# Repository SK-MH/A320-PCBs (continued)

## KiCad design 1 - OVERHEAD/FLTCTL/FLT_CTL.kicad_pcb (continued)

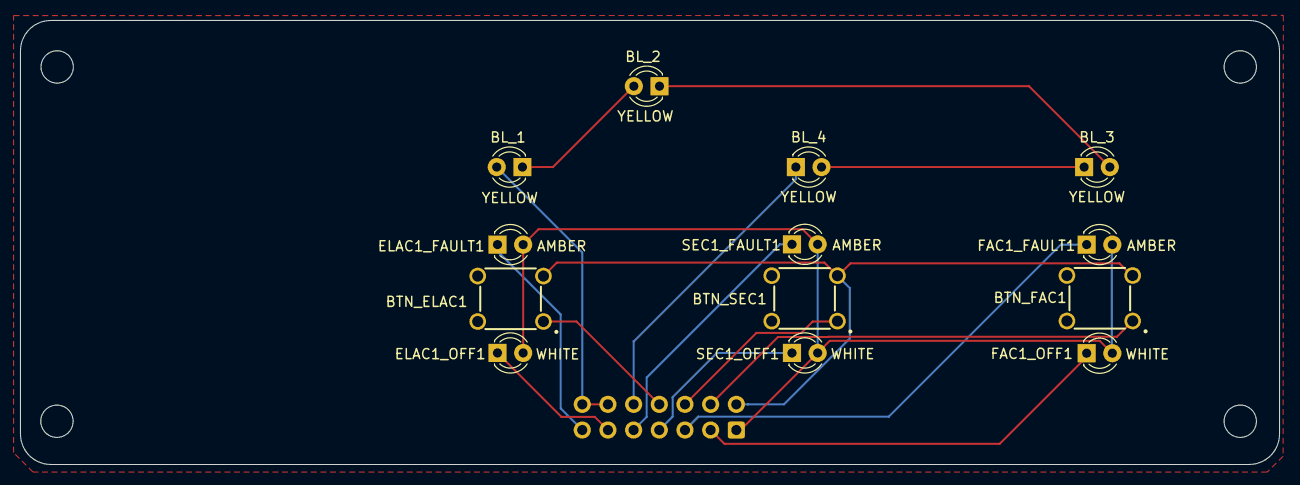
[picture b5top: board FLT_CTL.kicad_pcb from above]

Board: 2 copper layers, 124.6 x 43.9 mm, 14 parts (1 on the bottom side), 16 nets.

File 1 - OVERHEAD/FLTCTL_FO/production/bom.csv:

Designator,Footprint,Quantity,Value,LCSC Part #
"BL_1, BL_2, BL_3, BL_4",LED_D3.0mm,4,YELLOW,
"BTN_ELAC2, BTN_FAC2, BTN_SEC2, BTN_SEC3",B3F1000,4,B3F-1055,
"ELAC2_FAULT1, FAC2_FAULT1, SEC2_FAULT1, SEC3_FAULT1",LED_D3.0mm,4,AMBER,
"ELAC2_OFF1, FAC2_OFF1, SEC2_OFF1, SEC3_OFF1",LED_D3.0mm,4,WHITE,
FLT_CTL_FO1,IDC-Header_2x08_P2.54mm_Vertical,1,Pin Header,

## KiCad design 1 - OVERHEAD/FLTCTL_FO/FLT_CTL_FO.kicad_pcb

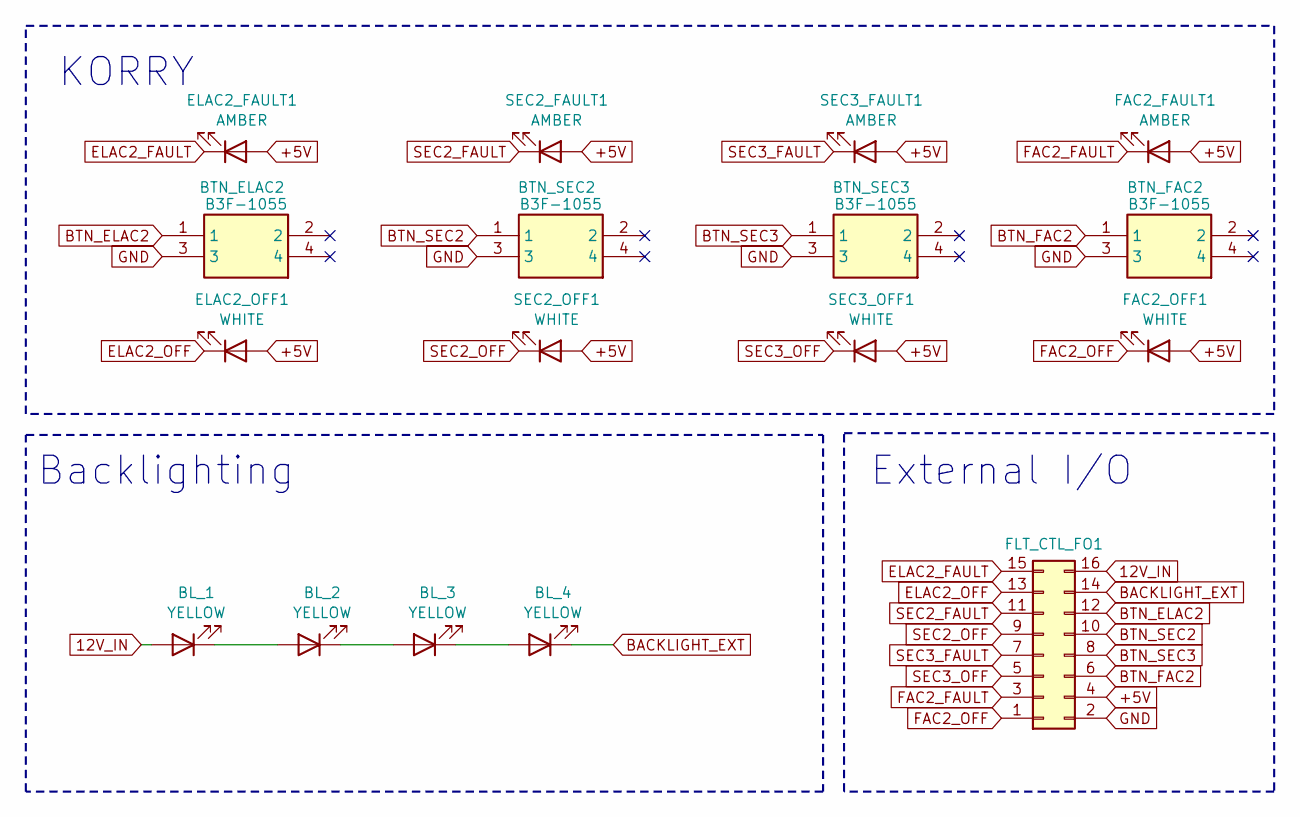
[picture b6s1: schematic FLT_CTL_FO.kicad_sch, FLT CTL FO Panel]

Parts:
BL_1, BL_2, BL_3, BL_4: YELLOW; LED_D3.0mm
BTN_ELAC2: B3F-1055; B3F1000; Mouser Part Number 653-B3F-1055
BTN_FAC2: B3F-1055; B3F1000; Mouser Part Number 653-B3F-1055
BTN_SEC2, BTN_SEC3: B3F-1055; B3F1000; Mouser Part Number 653-B3F-1055
ELAC2_FAULT1: AMBER; LED_D3.0mm
ELAC2_OFF1: WHITE; LED_D3.0mm
FAC2_FAULT1: AMBER; LED_D3.0mm
FAC2_OFF1: WHITE; LED_D3.0mm
FLT_CTL_FO1: Pin Header; IDC-Header_2x08_P2.54mm_Vertical
SEC2_FAULT1, SEC3_FAULT1: AMBER; LED_D3.0mm
SEC2_OFF1, SEC3_OFF1: WHITE; LED_D3.0mm

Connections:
12V_IN: BL_1.2 (A), FLT_CTL_FO1.16
+5V: ELAC2_FAULT1.2 (A), ELAC2_OFF1.2 (A), FAC2_FAULT1.2 (A), FAC2_OFF1.2 (A), FLT_CTL_FO1.4, SEC2_FAULT1.2 (A), SEC2_OFF1.2 (A), SEC3_FAULT1.2 (A), SEC3_OFF1.2 (A)
BACKLIGHT_EXT: BL_4.1 (K), FLT_CTL_FO1.14
BTN_ELAC2: BTN_ELAC2.1, FLT_CTL_FO1.12
BTN_FAC2: BTN_FAC2.1, FLT_CTL_FO1.6
BTN_SEC2: BTN_SEC2.1, FLT_CTL_FO1.10
BTN_SEC3: BTN_SEC3.1, FLT_CTL_FO1.8
ELAC2_FAULT: ELAC2_FAULT1.1 (K), FLT_CTL_FO1.15
ELAC2_OFF: ELAC2_OFF1.1 (K), FLT_CTL_FO1.13
FAC2_FAULT: FAC2_FAULT1.1 (K), FLT_CTL_FO1.3
FAC2_OFF: FAC2_OFF1.1 (K), FLT_CTL_FO1.1
GND: BTN_ELAC2.3, BTN_FAC2.3, BTN_SEC2.3, BTN_SEC3.3, FLT_CTL_FO1.2
unnamed: BL_1.1 (K), BL_2.2 (A)
unnamed: BL_2.1 (K), BL_3.2 (A)
unnamed: BL_3.1 (K), BL_4.2 (A)
SEC2_FAULT: FLT_CTL_FO1.11, SEC2_FAULT1.1 (K)
SEC2_OFF: FLT_CTL_FO1.9, SEC2_OFF1.1 (K)
SEC3_FAULT: FLT_CTL_FO1.7, SEC3_FAULT1.1 (K)
SEC3_OFF: FLT_CTL_FO1.5, SEC3_OFF1.1 (K)

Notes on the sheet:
Backlighting
External I/O
KORRY

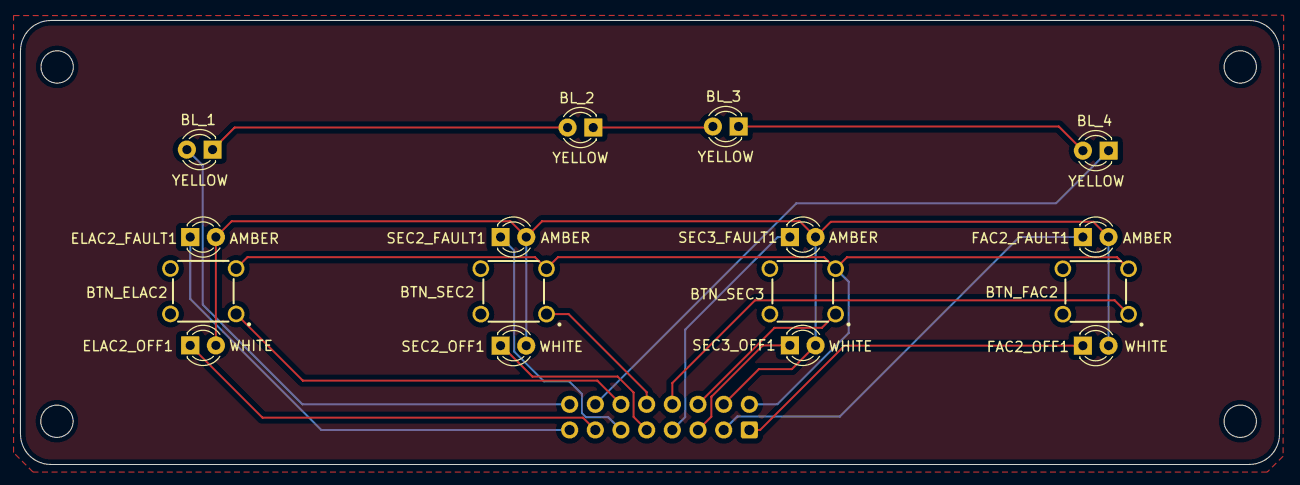
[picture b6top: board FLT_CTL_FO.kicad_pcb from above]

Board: 2 copper layers, 124.6 x 43.9 mm, 17 parts (1 on the bottom side), 19 nets.

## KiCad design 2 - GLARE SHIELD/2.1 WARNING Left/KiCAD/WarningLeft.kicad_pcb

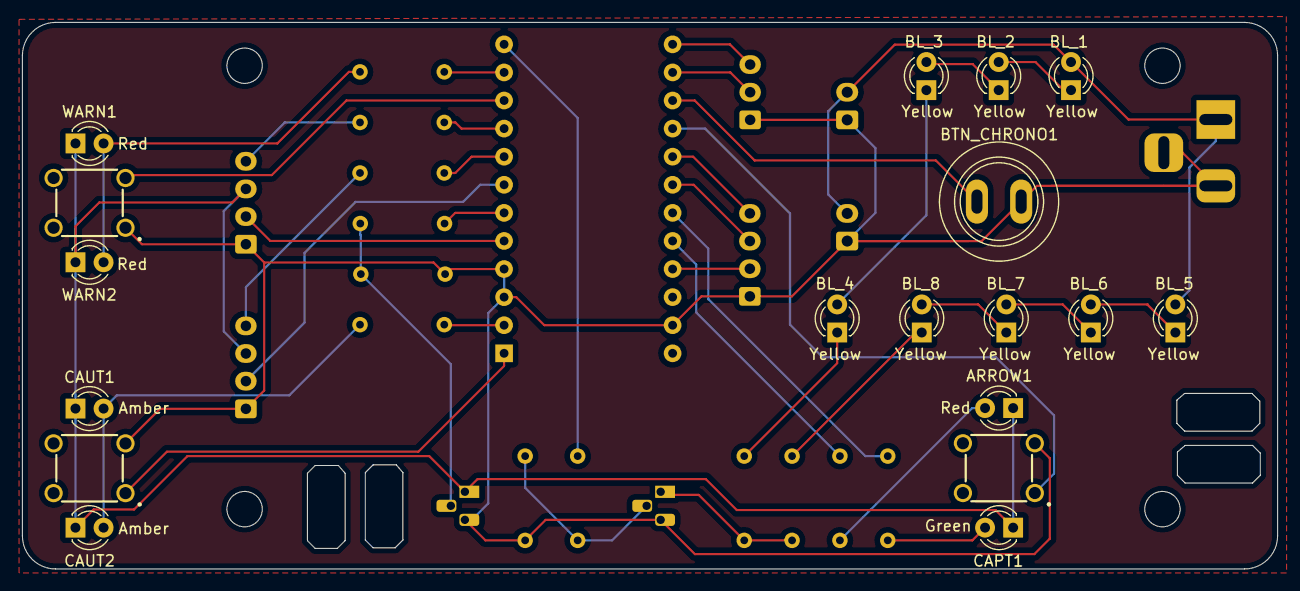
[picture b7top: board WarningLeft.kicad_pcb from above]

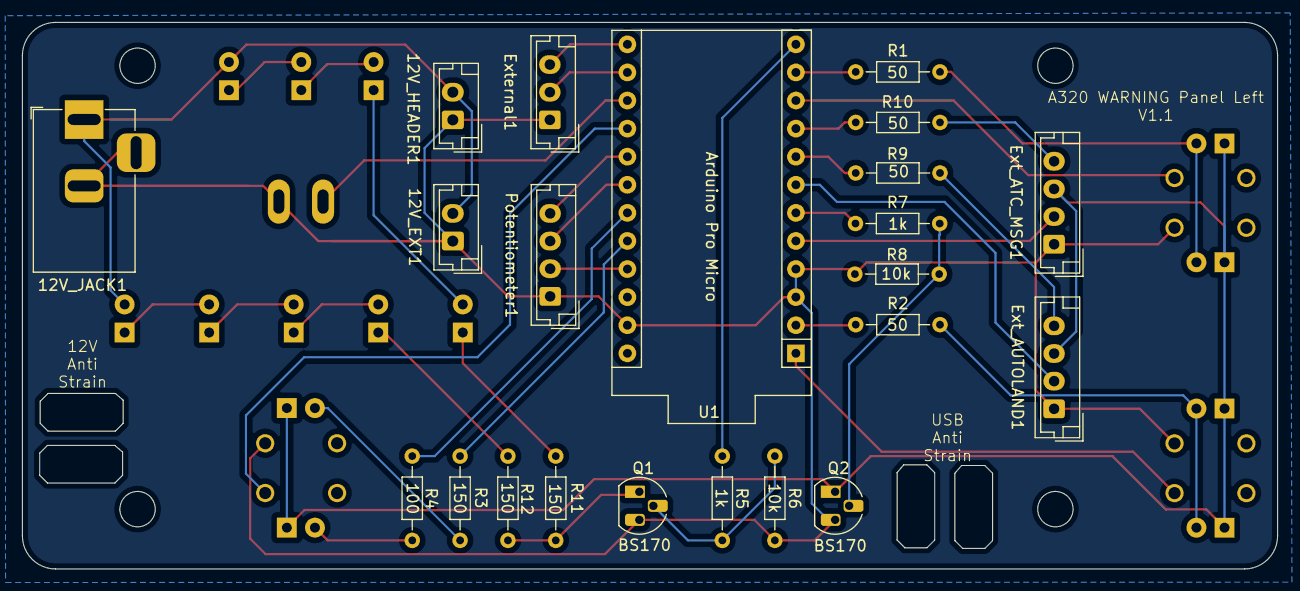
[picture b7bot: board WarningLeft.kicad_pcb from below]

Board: 2 copper layers, 113.5 x 49.4 mm, 40 parts (22 on the bottom side), 39 nets.

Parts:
12V_EXT1, 12V_HEADER1: Pin Header 1x02; JST_EH_B2B-EH-A_1x02_P2.50mm_Vertical
12V_JACK1: Power Jack; BarrelJack_Horizontal
ARROW1: Red; LED_D3.0mm
BL_1, BL_2, BL_3, BL_4, BL_5, BL_6, BL_7, BL_8: Yellow; LED_D3.0mm
BTN_CAUT1: B3F-1055; B3F1000
BTN_CHRONO1: Push Button; SW-Push
BTN_SIDESTICK1: B3F-1055; B3F1000
BTN_WARN1: B3F-1055; B3F1000
CAPT1: Green; LED_D3.0mm
CAUT1, CAUT2: Amber; LED_D3.0mm
Ext_ATC_MSG1: Pin Header 1x04; JST_EH_B4B-EH-A_1x04_P2.50mm_Vertical
Ext_AUTOLAND1: Pin Header 1x04; JST_EH_B4B-EH-A_1x04_P2.50mm_Vertical
External1: Pin Header 1x03; JST_EH_B3B-EH-A_1x03_P2.50mm_Vertical
Potentiometer1: Pin Header 1x04; JST_EH_B4B-EH-A_1x04_P2.50mm_Vertical
Q1, Q2: BS170; TO-92_HandSolder
R1, R2, R9, R10: 50; R_Axial_DIN0204_L3.6mm_D1.6mm_P7.62mm_Horizontal
R3, R11, R12: 150; R_Axial_DIN0204_L3.6mm_D1.6mm_P7.62mm_Horizontal
R4: 100; R_Axial_DIN0204_L3.6mm_D1.6mm_P7.62mm_Horizontal
R5, R7: 1k; R_Axial_DIN0204_L3.6mm_D1.6mm_P7.62mm_Horizontal
R6, R8: 10k; R_Axial_DIN0204_L3.6mm_D1.6mm_P7.62mm_Horizontal
U1: Arduino Pro Micro; Sparkfun_Pro_Micro
WARN1, WARN2: Red; LED_D3.0mm

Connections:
12V_IN: 12V_EXT1.2, 12V_HEADER1.2, 12V_JACK1.1, BL_1.2 (A), BL_5.2 (A)
+5V: Potentiometer1.2, U1.21 (VCC)
ARROW: R3.1, U1.20 (D21/A3)
ATC_MSG: R10.2, U1.9 (~D6/A7)
AUTOLAND: R9.2, U1.8 (~D5)
BACKLIGHT_GND: Q1.1 (D), R11.2, R12.2
BTN_ATC_MSG: Ext_ATC_MSG1.2, U1.5 (D2)
BTN_AUTOLAND: Ext_AUTOLAND1.2, U1.7 (D4/A6)
BTN_CAUT: BTN_CAUT1.1, U1.1 (D1/TX)
BTN_CHRONO: BTN_CHRONO1.1, U1.15 (D14)
BTN_SIDESTICK: BTN_SIDESTICK1.1, U1.16 (D15)
BTN_WARN: BTN_WARN1.3, U1.10 (D7)
CAUT: R2.1, U1.2 (D0/RX)
EXT1: External1.2, U1.14 (D16)
EXT2: External1.3, U1.13 (~D10/A10)
GND: 12V_EXT1.1, 12V_HEADER1.1, 12V_JACK1.2, 12V_JACK1.3, BTN_CAUT1.3, BTN_CHRONO1.2, BTN_SIDESTICK1.3, BTN_WARN1.1, Ext_ATC_MSG1.1, Ext_AUTOLAND1.1, External1.1, Potentiometer1.1, Q1.3 (S), Q2.3 (S), R6.1, R8.1, U1.3 (GND), U1.4 (GND), U1.23 (GND)
LED_GND: ARROW1.1 (K), CAPT1.1 (K), CAUT1.1 (K), CAUT2.1 (K), Ext_ATC_MSG1.3, Ext_AUTOLAND1.3, Q2.1 (D), WARN1.1 (K), WARN2.1 (K)
unnamed: ARROW1.2 (A), R3.2
unnamed: BL_1.1 (K), BL_2.2 (A)
unnamed: BL_2.1 (K), BL_3.2 (A)
unnamed: BL_3.1 (K), BL_4.2 (A)
unnamed: BL_4.1 (K), R11.1
unnamed: BL_5.1 (K), BL_6.2 (A)
unnamed: BL_6.1 (K), BL_7.2 (A)
unnamed: BL_7.1 (K), BL_8.2 (A)
unnamed: BL_8.1 (K), R12.1
unnamed: CAPT1.2 (A), R4.2
unnamed: CAUT1.2 (A), CAUT2.2 (A), R2.2
unnamed: Ext_ATC_MSG1.4, R10.1
unnamed: Ext_AUTOLAND1.4, R9.1
unnamed: Q1.2 (G), R5.2, R6.2
unnamed: Q2.2 (G), R7.2, R8.2
unnamed: R1.2, WARN1.2 (A), WARN2.2 (A)
OUT_BRT_BACK: R5.1, U1.12 (~D9/A9)
OUT_BRT_LED: R7.1, U1.6 (~D3)
POT1: Potentiometer1.3, U1.18 (D19/A1)
POT2: Potentiometer1.4, U1.17 (D18/A0)
PRIO: R4.1, U1.19 (D20/A2)
WARN: R1.1, U1.11 (D8/A8)

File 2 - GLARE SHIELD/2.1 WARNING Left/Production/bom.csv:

Designator,Footprint,Quantity,Value,LCSC Part #
"12V_EXT1, 12V_HEADER1",JST_EH_B2B-EH-A_1x02_P2.50mm_Vertical,2,Pin Header 1x02,
12V_JACK1,BarrelJack_Horizontal,1,Power Jack,
"ARROW1, WARN1, WARN2",LED_D3.0mm,3,Red,
"BL_1, BL_2, BL_3, BL_4, BL_5, BL_6, BL_7, BL_8",LED_D3.0mm,8,Yellow,
"BTN_CAUT1, BTN_SIDESTICK1, BTN_WARN1",B3F1000,3,B3F-1055,
BTN_CHRONO1,SW-Push,1,Push Button,
CAPT1,LED_D3.0mm,1,Green,
"CAUT1, CAUT2",LED_D3.0mm,2,Amber,
"Ext_ATC_MSG1, Ext_AUTOLAND1, Potentiometer1",JST_EH_B4B-EH-A_1x04_P2.50mm_Vertical,3,Pin Header 1x04,
External1,JST_EH_B3B-EH-A_1x03_P2.50mm_Vertical,1,Pin Header 1x03,
"Q1, Q2",TO-92_HandSolder,2,BS170,
"R1, R10, R2, R9",R_Axial_DIN0204_L3.6mm_D1.6mm_P7.62mm_Horizontal,4,50,
"R11, R12, R3",R_Axial_DIN0204_L3.6mm_D1.6mm_P7.62mm_Horizontal,3,150,
R4,R_Axial_DIN0204_L3.6mm_D1.6mm_P7.62mm_Horizontal,1,100,
"R5, R7",R_Axial_DIN0204_L3.6mm_D1.6mm_P7.62mm_Horizontal,2,1k,
"R6, R8",R_Axial_DIN0204_L3.6mm_D1.6mm_P7.62mm_Horizontal,2,10k,
U1,Sparkfun_Pro_Micro,1,Arduino Pro Micro,

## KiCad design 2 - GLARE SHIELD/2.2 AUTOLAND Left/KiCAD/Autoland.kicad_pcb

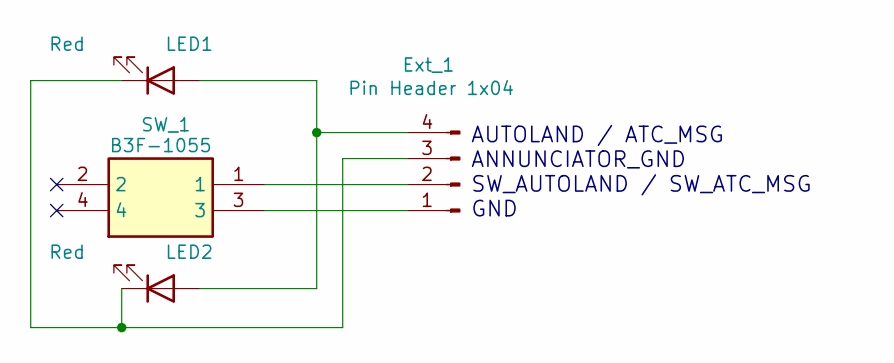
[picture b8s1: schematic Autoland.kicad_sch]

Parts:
Ext_1: Pin Header 1x04; JST_EH_B4B-EH-A_1x04_P2.50mm_Vertical
LED1, LED2: Red; LED_D3.0mm
SW_1: B3F-1055; B3F1000; Mouser Part Number 653-B3F-1055

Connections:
unnamed: Ext_1.1, SW_1.3
unnamed: Ext_1.2, SW_1.1
unnamed: Ext_1.3, LED1.1 (K), LED2.1 (K)
unnamed: Ext_1.4, LED1.2 (A), LED2.2 (A)

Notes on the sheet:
AUTOLAND / ATC_MSG ANNUNCIATOR_GND SW_AUTOLAND / SW_ATC_MSG GND

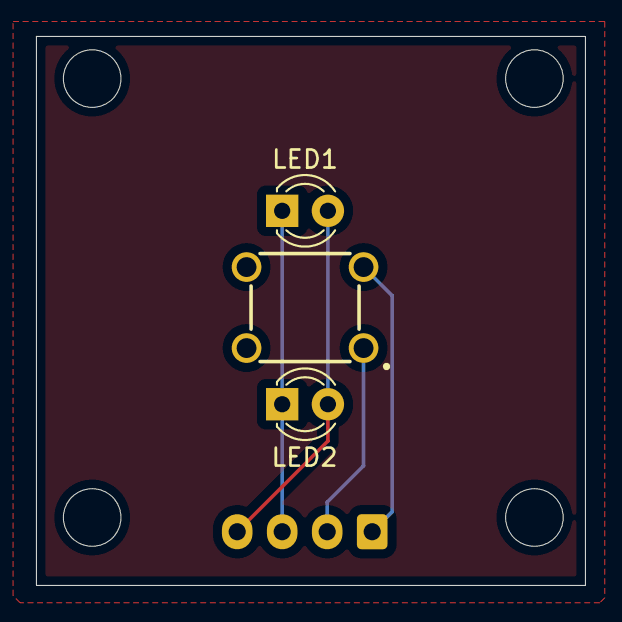
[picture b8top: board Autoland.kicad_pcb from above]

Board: 2 copper layers, 30.5 x 30.5 mm, 4 parts (1 on the bottom side), 4 nets.

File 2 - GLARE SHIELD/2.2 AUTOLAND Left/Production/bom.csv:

Designator,Footprint,Quantity,Value,LCSC Part #
Ext_1,JST_EH_B4B-EH-A_1x04_P2.50mm_Vertical,1,Pin Header 1x04,
"LED1, LED2",LED_D3.0mm,2,Red,
SW_1,B3F1000,1,B3F-1055,
